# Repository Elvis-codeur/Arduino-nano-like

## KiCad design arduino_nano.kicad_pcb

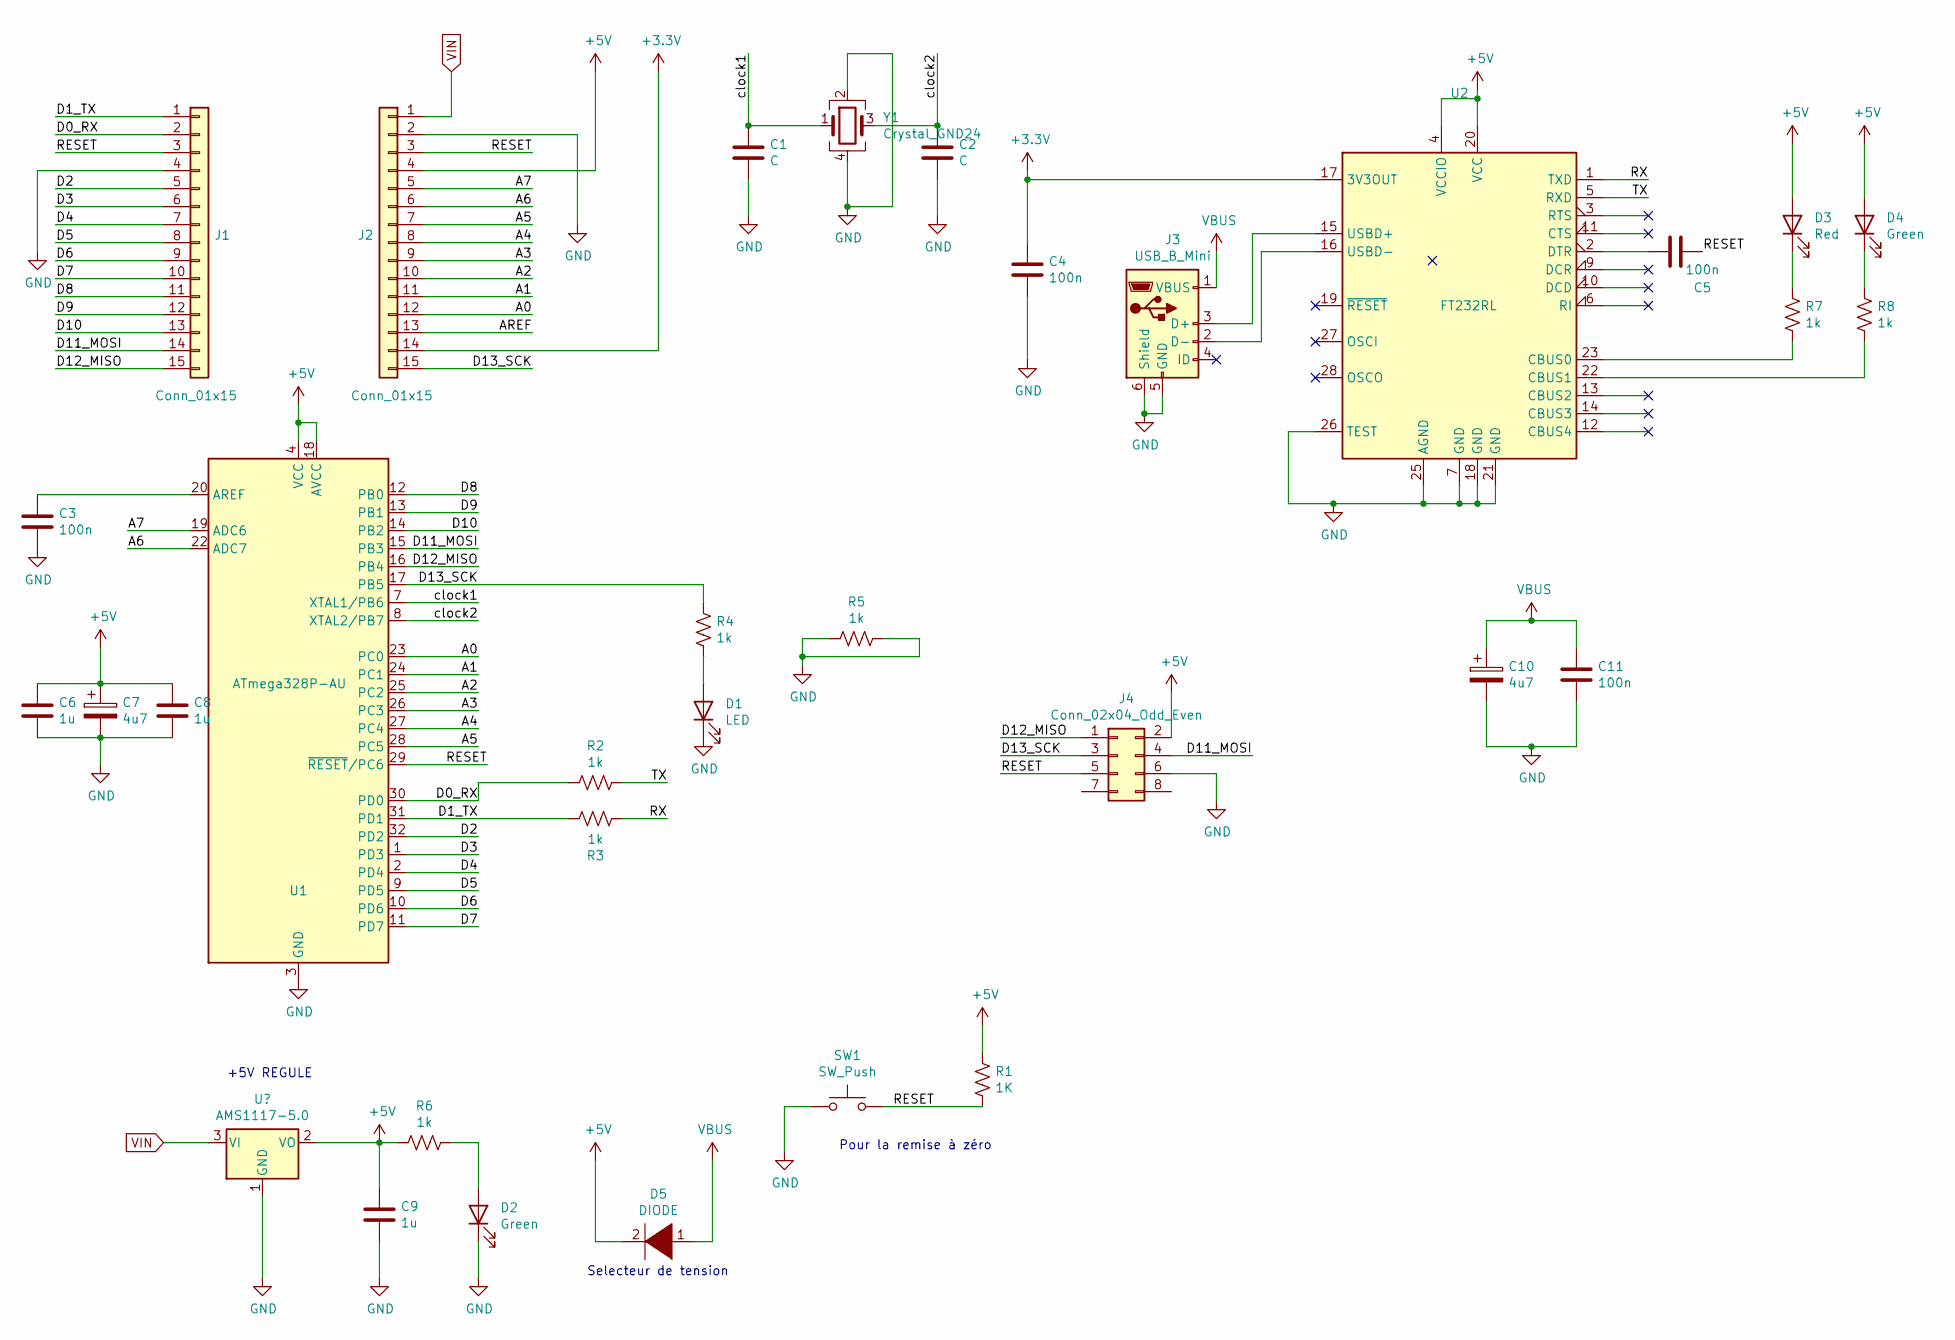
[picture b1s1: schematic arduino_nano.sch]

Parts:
C1, C2: C; C_0402_1005Metric
C3, C4, C5, C11: 100n; C_0402_1005Metric
C6, C8, C9: 1u; C_0402_1005Metric
C7, C10: 4u7; C_0402_1005Metric
D1: LED; D_0603_1608Metric_Pad1.05x0.95mm_HandSolder
D2, D4: Green; D_0603_1608Metric_Pad1.05x0.95mm_HandSolder
D3: Red; D_0603_1608Metric_Pad1.05x0.95mm_HandSolder
D5: DIODE; D_0603_1608Metric_Pad1.05x0.95mm_HandSolder
J1, J2: Conn_01x15; PinHeader_1x15_P2.54mm_Vertical
J3: USB_B_Mini; USB_Micro-B_Wuerth_629105150521
J4: Conn_02x04_Odd_Even; PinHeader_2x04_P2.54mm_Vertical
R1: 1K; R_0402_1005Metric
R2, R3, R4, R5, R6, R7, R8: 1k; R_0402_1005Metric
SW1: SW_Push; SW_DIP_SPSTx01_Slide_6.7x4.1mm_W6.73mm_P2.54mm_LowProfile_J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
U1: ATmega328P-AU; TQFP-32_7x7mm_P0.8mm
U2: FT232RL; SSOP-28_5.3x10.2mm_P0.65mm
Y1: Crystal_GND24; Crystal_SMD_3225-4Pin_3.2x2.5mm

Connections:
+3V3: C4.1, J2.14, U2.17 (3V3OUT)
+5V: C6.1, C7.1, C8.1, C9.1, D3.2 (A), D4.2 (A), D5.2 (A), J2.4, J4.2, R1.1, R6.2, U1.4 (VCC), U1.6 (VCC), U1.18 (AVCC), U2.4 (VCCIO), U2.20 (VCC); also elsewhere on the board
/A0: J2.12, U1.23 (PC0)
/A1: J2.11, U1.24 (PC1)
/A2: J2.10, U1.25 (PC2)
/A3: J2.9, U1.26 (PC3)
/A4: J2.8, U1.27 (PC4)
/A5: J2.7, U1.28 (PC5)
/A6: J2.6, U1.22 (ADC7)
/A7: J2.5, U1.19 (ADC6)
/AREF: J2.13
/D0_RX: J1.2, R2.1, U1.30 (PD0)
/D1_TX: J1.1, R3.1, U1.31 (PD1)
/D2: J1.5, U1.32 (PD2)
/D3: J1.6, U1.1 (PD3)
/D4: J1.7, U1.2 (PD4)
/D5: J1.8, U1.9 (PD5)
/D6: J1.9, U1.10 (PD6)
/D7: J1.10, U1.11 (PD7)
/D8: J1.11, U1.12 (PB0)
/D9: J1.12, U1.13 (PB1)
/D10: J1.13, U1.14 (PB2)
/D11_MOSI: J1.14, J4.4, U1.15 (PB3)
/D12_MISO: J1.15, J4.1, U1.16 (PB4)
/D13_SCK: J2.15, J4.3, R4.1, U1.17 (PB5)
/RESET: C5.1, J1.3, J2.3, J4.5, R1.2, SW1.2, U1.29 (~RESET~/PC6)
/RX: R3.2, U2.1 (TXD)
/TX: R2.2, U2.5 (RXD)
/clock1: C1.1, U1.7 (XTAL1/PB6), Y1.1
/clock2: C2.1, U1.8 (XTAL2/PB7), Y1.3
GND: C1.2, C2.2, C3.2, C4.2, C6.2, C7.2, C8.2, C9.2, C10.2, C11.2, D1.1 (K), D2.1 (K), J1.4, J2.2, J3.5 (GND), J3.6 (Shield), J4.6, R5.1, R5.2, SW1.1, U1.3 (GND), U1.5 (GND), U1.21 (GND), U2.7 (GND), U2.18 (GND), U2.21 (GND), U2.25 (AGND), U2.26 (TEST), Y1.2, Y1.4; also elsewhere on the board
unnamed: C3.1, U1.20 (AREF)
unnamed: C5.2, U2.2 (DTR)
unnamed: D1.2 (A), R4.2
unnamed: D2.2 (A), R6.1
unnamed: D3.1 (K), R7.1
unnamed: D4.1 (K), R8.1
unnamed: J3.2 (D-), U2.16 (USBD-)
unnamed: J3.3 (D+), U2.15 (USBD+)
unnamed: R7.2, U2.23 (CBUS0)
unnamed: R8.2, U2.22 (CBUS1)
VBUS: C10.1, C11.1, D5.1 (K), J3.1 (VBUS)
VIN: J2.1; also elsewhere on the board

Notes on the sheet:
Pour la remise à zéro
+5V REGULE
Selecteur de tension

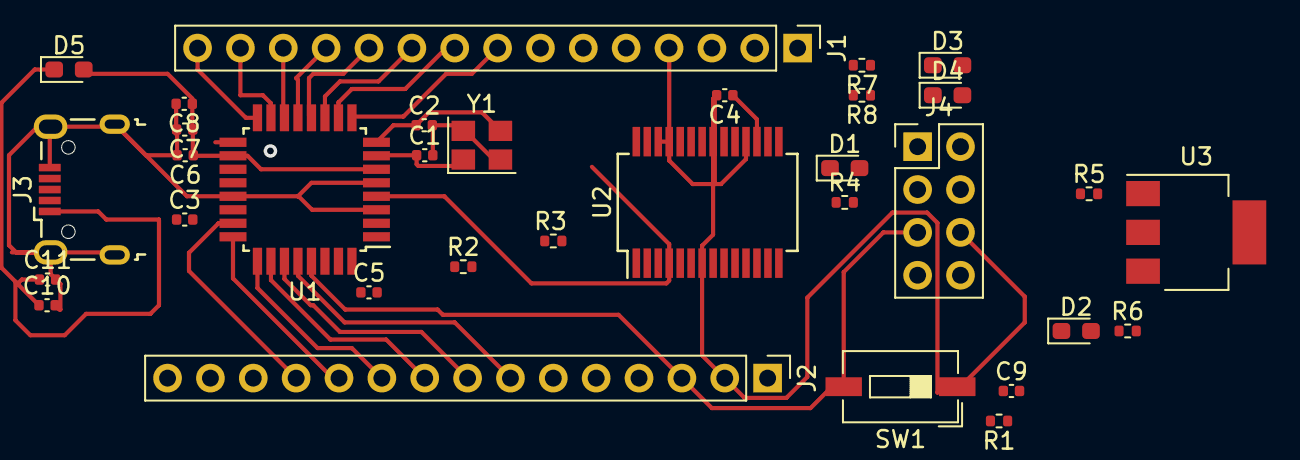
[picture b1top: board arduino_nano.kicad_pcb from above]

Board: 2 copper layers, 33 parts (0 on the bottom side), 42 nets.

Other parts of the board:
U3: AMS1117-5.0; SOT-223-3_TabPin2

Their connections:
+5V: U3.2; also elsewhere on the board
GND: U3.1; also elsewhere on the board
VIN: U3.3; also elsewhere on the board

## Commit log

2021-11-08 Premier commit 8/11/2021
